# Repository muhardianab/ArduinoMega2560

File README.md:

# ArduinoMega2560
 Making a new Arduino Mega 2560 Board

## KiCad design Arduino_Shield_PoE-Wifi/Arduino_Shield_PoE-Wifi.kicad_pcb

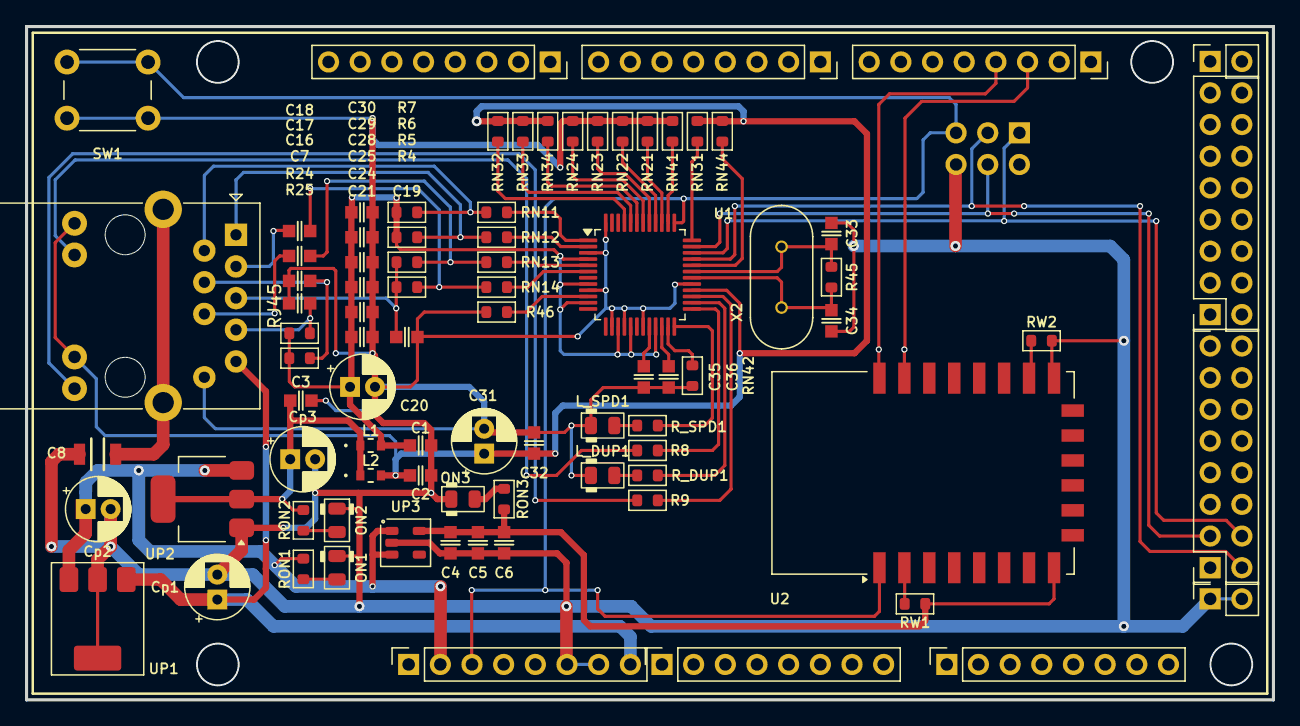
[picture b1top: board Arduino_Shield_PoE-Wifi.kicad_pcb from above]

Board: 2 copper layers, 100.0 x 54.0 mm, 86 parts (1 on the bottom side), 56 nets.

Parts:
ADC1, ADC2: PINHD_1x8_Female; PinSocket_1x08_P2.54mm_Vertical
C1, C2, C3, C4, C5, C6: 100nF_0603_16V; C_0603
C7, C19: 10nF_0603_16V; C_0603
C8: 1nF 2KV 1206; C_1206
C16: 22nF_0603_16V; C_0603
C17, C18: 6.8nF_0603_16V; C_0603
C20, C31: 10uF_25V; CP_Radial_D5.0mm_P2.00mm
C21, C24, C25, C28, C29, C30, C32, C36: 0.1uF_0603_16V; C_0603
C33, C34: 18pF_0603_16V; C_0603
C35: 4.7uF_0603_16V; C_0603
COM1: PINHD_1x8_Female; PinSocket_1x08_P2.54mm_Vertical
Cp1, Cp2, Cp3: 10uF_25V; CP_Radial_D5.0mm_P2.00mm
ICSP1: ICSP_Connector_Female; PinSocket_2x03_P2.54mm_Vertical
J1, J2: Conn_02x08; PinSocket_2x08_P2.54mm_Vertical
J3, J4: PINHD_1x2_Female; PinSocket_1x02_P2.54mm_Vertical
L1, L2: MPZ1608S101ATAH0; IND_1608_TDK
L_DUP1: LED_0805_RED; LED_0805_2012Metric
L_SPD1: LED_0805_RED; LED_0805_2012Metric
ON1, ON2, ON3: LED_0805_Green; LED_0805_2012Metric
PWM1, PWM2: PINHD_1x8_Female; PinSocket_1x08_P2.54mm_Vertical
PWR1: PINHD_1x8_Female; PinSocket_1x08_P2.54mm_Vertical
R4, R5, R6, R7: 49R9_0603; R_0603_1608Metric
R8, R9: 330R_0603; R_0603_1608Metric
R24: 22R_0603; R_0603_1608Metric
R25: 10R_0603; R_0603_1608Metric
R45: 1M_0603; R_0603_1608Metric
R46: 12.4K_0603; R_0603_1608Metric
RJ45: RJ45_Abracon_ARJP11A-MASA-B-A-EMU2; RJ45_Abracon_ARJP11A-MA_Horizontal-edited
RN11, RN12, RN13, RN14: 33R_0603; R_0603_1608Metric
RN21, RN22, RN23, RN24, RN31, RN32, RN33, RN34, RN41, RN42, RN44: 10K_0603; R_0603_1608Metric
RON1, RON2, RON3: 1K_0603; R_0603_1608Metric
RW1, RW2: 10K_0603; R_0603_1608Metric
R_DUP1: 1K_0603; R_0603_1608Metric
R_SPD1: 1K_0603; R_0603_1608Metric
SW1: Push_Button; SW_PUSH_6mm
U1: W5500; LQFP-48_7x7mm_P0.5mm
U2: ESP-12E
UP1: LM7805MP; SOT-223-3_TabPin2
UP2: AMS1117-3.3; SOT-223-3_TabPin2
UP3: AP2112K-3.3TRG1; SOT-23-5
X2: 25MHz 18pF; XTAL_HC49P488W46L1150T500H350

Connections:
+3V3A: C1.1, C20.1, C21.1, C24.1, C25.1, C28.1, C29.1, C30.1, L1.2, R6.2, R7.2, R24.1, R25.1, U1.4 (AVDD), U1.8 (AVDD), U1.11 (AVDD), U1.15 (AVDD), U1.17 (AVDD), U1.21 (AVDD)
+3V3B: C2.1, C31.1, C32.1, L2.2, RJ45.11, RJ45.13, RN31.1, RN32.1, RN33.1, RN34.1, RN44.1, U1.28 (VDD)
+3V3C: C4.1, C5.1, C6.1, RON3.2, RW1.1, U2.8 (VCC), UP3.5 (OUT)
+5V: Cp2.1, ICSP1.2 (VCC), J3.1, J3.2, PWR1.2, PWR1.5, RON1.2, UP1.3 (OUT), UP2.3 (VI), UP3.1 (IN), UP3.3 (EN)
/PB1: ICSP1.3 (SCK), J1.2, U1.33 (SCLK)
/PB2: ICSP1.4 (MOSI), J1.3, U1.35 (MOSI)
/PB3: ICSP1.1 (MISO), J1.4, U1.34 (MISO)
/PowerOverEthernet/ACT_LED: R9.1, U1.27 (ACTLED)
/PowerOverEthernet/DUP_LED: R_DUP1.2, U1.26 (DUPLED)
/PowerOverEthernet/INT: RN31.2, U1.36 (~INT)
/PowerOverEthernet/LINK_LED: R8.1, U1.25 (LINKLED)
/PowerOverEthernet/RCT: C19.2, R4.2, R5.2, RJ45.5 (RCT)
/PowerOverEthernet/RSVD1: RN41.1, U1.38 (RSVD)
/PowerOverEthernet/RSVD2: RN21.1, U1.39 (RSVD)
/PowerOverEthernet/RSVD3: RN22.1, U1.40 (RSVD)
/PowerOverEthernet/RSVD4: RN23.1, U1.41 (RSVD)
/PowerOverEthernet/RSVD5: RN24.1, U1.42 (RSVD)
/PowerOverEthernet/RSVD6: RN42.1, U1.23 (RSVD)
/PowerOverEthernet/RXN1: RN13.1, U1.5 (RXN)
/PowerOverEthernet/RXN2: C17.1, R5.1, RN13.2
/PowerOverEthernet/RXP1: RN14.1, U1.6 (RXP)
/PowerOverEthernet/RXP2: C18.1, R4.1, RN14.2
/PowerOverEthernet/SCS: RN44.2, U1.32 (~SCS)
/PowerOverEthernet/SPD_LED: R_SPD1.2, U1.24 (SPDLED)
/PowerOverEthernet/TCT: C16.2, R25.2, RJ45.4 (TCT)
/PowerOverEthernet/TXN1: RN11.1, U1.1 (TXN)
/PowerOverEthernet/TXN2: R7.1, RJ45.2 (TD-), RN11.2
/PowerOverEthernet/TXP1: RN12.1, U1.2 (TXP)
/PowerOverEthernet/TXP2: R6.1, RJ45.1 (TD+), RN12.2
/RESET1: ICSP1.5 (~{RST), PWR1.3, SW1.1, U1.37 (~RST), U2.1 (~RST)
/RXD1: COM1.3, U2.21 (GPIO3/RXD)
/TXD1: COM1.4, U2.22 (GPIO1/TXD)
Earth: C8.2, RJ45.SH
GND: C1.2, C2.2, C3.2, C4.2, C5.2, C6.2, C7.1, C8.1, C16.1, C19.1, C20.2, C21.2, C24.2, C25.2, C28.2, C29.2, C30.2, C31.2, C32.2, C33.2, C34.2, C35.1, C36.2, Cp1.2, Cp2.2, Cp3.2, ICSP1.6 (GND), J4.1, J4.2, L_DUP1.1 (K), L_SPD1.1 (K), ON1.1 (K), ON2.1 (K), ON3.1 (K), PWR1.6, PWR1.7, R46.2, RJ45.10 (V-), RN21.2, RN22.2, RN23.2, RN24.2, RN41.2, RN42.2, RW2.2, SW1.2, U1.3 (AGND), U1.9 (AGND), U1.14 (AGND), U1.16 (AGND), U1.19 (AGND), U1.29 (GND), U1.48 (AGND), U2.15 (GND), UP1.2, UP2.1 (GND), UP3.2
unnamed: C7.2, R24.2, RJ45.7
unnamed: L_DUP1.2 (A), R_DUP1.1
unnamed: L_SPD1.2 (A), R_SPD1.1
unnamed: ON1.2 (A), RON1.1
unnamed: ON2.2 (A), RON2.1
unnamed: ON3.2 (A), RON3.1
unnamed: R8.2, RJ45.12
unnamed: R9.2, RJ45.14
unnamed: C18.2, RJ45.3 (RD+)
unnamed: C17.2, RJ45.6 (RD-)
unnamed: C36.1, U1.22 (1V2O)
unnamed: R46.1, U1.10 (EXRES1)
unnamed: RN32.2, U1.45 (PMODE0)
unnamed: RN33.2, U1.44 (PMODE1)
unnamed: RN34.2, U1.43 (PMODE2)
unnamed: C35.2, U1.20 (TOCAP)
unnamed: C34.1, R45.2, U1.30 (XI/CLKIN), X2.1
unnamed: C33.1, R45.1, U1.31 (XO), X2.2
unnamed: RW1.2, U2.2 (ADC)
unnamed: RW2.1, U2.16 (GPIO15)
unnamed: C3.1, Cp3.1, L1.1, L2.1, RON2.2, UP2.2 (VO)
VIN: Cp1.1, PWR1.8, RJ45.9 (V+), UP1.1 (IN)

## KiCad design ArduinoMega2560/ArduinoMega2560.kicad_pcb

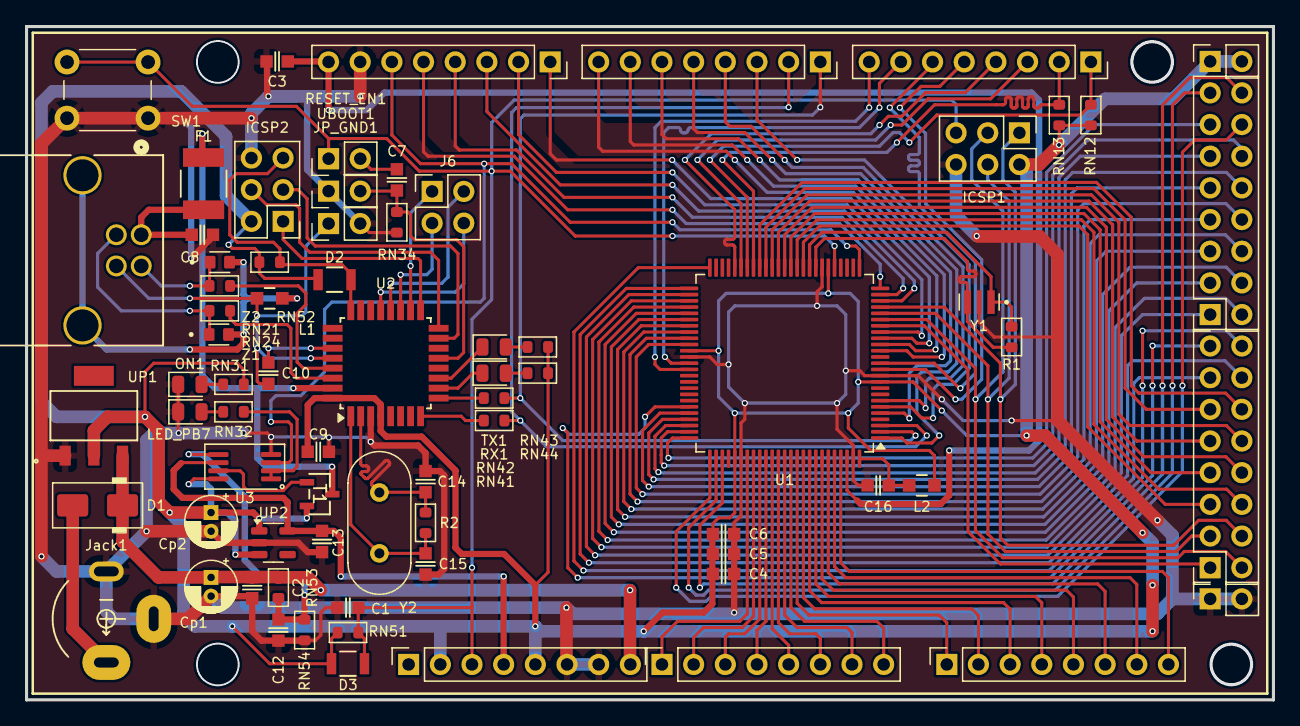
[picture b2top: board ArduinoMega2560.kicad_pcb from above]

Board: 2 copper layers, 100.0 x 54.0 mm, 73 parts (0 on the bottom side), 112 nets.

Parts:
ADC1, ADC2: PINHD_1x8_Female; PinSocket_1x08_P2.54mm_Vertical
C1: 22pF_0603_16V; C_0603
C2, C3, C4, C5, C6, C7, C8, C9, C10, C12, C13, C14, C15, C16: 100nF_0603_16V; C_0603
COM1: PINHD_1x8_Female; PinSocket_1x08_P2.54mm_Vertical
Cp1, Cp2: 47uF_10V; CP_Radial_D4.0mm_P1.50mm
D1: M7; D_SMA
D2, D3: CD1206-S01575; DIODE_CD1206-S01575_BRN
F1: MF-MSMF050-2; FUSE_F050-2
ICSP1, ICSP2: ICSP_Connector; PinHeader_2x03_P2.54mm_Vertical
J1, J2: Conn_02x08; PinSocket_2x08_P2.54mm_Vertical
J3, J4: PINHD_1x2_Female; PinSocket_1x02_P2.54mm_Vertical
J6: PINHD_2x2_Male; PinHeader_2x02_P2.54mm_Vertical
JP_GND1: SolderJumper_2_Open; PinHeader_1x02_P2.54mm_Vertical
Jack1: Barrel_2.0mmPin_PJ064; Barrel_Vert_PJ064_slotted
L1, L2: MH2029-300Y; IND_BOURNS_MH2029
LED_PB7: Yellow 0805; LED_0805_2012Metric
ON1: Green 0805; LED_0805_2012Metric
PWM1, PWM2: PINHD_1x8_Female; PinSocket_1x08_P2.54mm_Vertical
PWR1: PINHD_1x8_Female; PinSocket_1x08_P2.54mm_Vertical
R1, R2: 1M_0603; R_0603_1608Metric
RESET_EN1: SolderJumper_2_Open; PinHeader_1x02_P2.54mm_Vertical
RN12, RN13, RN51, RN52, RN53, RN54: 10K_0603; R_0603_1608Metric
RN21, RN24: 22R_0603; R_0603_1608Metric
RN31, RN32, RN34, RN41, RN42, RN43, RN44: 1K_0603; R_0603_1608Metric
RX1: Yellow 0805; LED_0805_2012Metric
SW1: Push_Button; SW_PUSH_6mm
T1: PMV48XP_215; TO-236_SOT23_NEX
TX1: Green 0805; LED_0805_2012Metric
U1: ATmega2560-16A; TQFP-100_14x14mm_P0.5mm
U2: ATmega8U2-A; TQFP-32_7x7mm_P0.8mm
U3: LMV358IDGK; MSOP-8_3x3mm_P0.65mm
UBOOT1: SolderJumper_2_Open; PinHeader_1x02_P2.54mm_Vertical
UP1: LD1117S50CTR; SOT-223_STM
UP2: LP2985-3.3; SOT-23-5
USB1: UJ2-BH-1-TH; UJ2-BH-1-TH_CUD
Y1: CSTCE16M0V53-R0; OSC_CSTCE16M0V53-R0
Y2: Crystal_16MHz; Crystal_HC49-4H_Vertical
Z1, Z2: CG0603MLC-05E; VARC1608X56N

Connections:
+3V3: C13.1, PWR1.4, U3.6 (-), UP2.5 (VOUT)
+5V: C4.1, C5.1, C6.1, C9.1, Cp2.1, D2.1, D3.1, ICSP1.2 (VCC), ICSP2.2 (VCC), J3.1, J3.2, L2.2, PWR1.2, PWR1.5, RN12.2, RN13.2, RN31.2, RN43.2, RN44.2, RN51.2, RN52.2, T1.2 (S), U1.10 (VCC), U1.31 (VCC), U1.61 (VCC), U1.80 (VCC), U2.4 (VCC), U2.32 (AVCC), U3.8 (V+), UP1.2 (VOUT), UP2.1 (VIN), UP2.3 (ON/~OFF)
/ADC0: ADC2.8, U1.97 (PF0)
/ADC1: ADC2.7, U1.96 (PF1)
/ADC2: ADC2.6, U1.95 (PF2)
/ADC3: ADC2.5, U1.94 (PF3)
/ADC4: ADC2.4, U1.93 (PF4)
/ADC5: ADC2.3, U1.92 (PF5)
/ADC6: ADC2.2, U1.91 (PF6)
/ADC7: ADC2.1, U1.90 (PF7)
/ADC8: ADC1.8, U1.89 (PK0)
/ADC9: ADC1.7, U1.88 (PK1)
/ADC10: ADC1.6, U1.87 (PK2)
/ADC11: ADC1.5, U1.86 (PK3)
/ADC12: ADC1.4, U1.85 (PK4)
/ADC13: ADC1.3, U1.84 (PK5)
/ADC14: ADC1.2, U1.83 (PK6)
/ADC15: ADC1.1, U1.82 (PK7)
/ATmega8U2-MU/MISO2: ICSP2.1 (MISO), U2.17 (PB3)
/ATmega8U2-MU/MOSI2: ICSP2.4 (MOSI), U2.16 (PB2)
/ATmega8U2-MU/SCK2: ICSP2.3 (SCK), U2.15 (PB1)
/ATmega8U2-MU/XT1: C15.2, R2.2, U2.1 (XTAL1), Y2.1
/ATmega8U2-MU/XT2: C14.2, R2.1, U2.2 (PC0/XTAL2), Y2.2
/PA0: J2.16, U1.78 (PA0)
/PA1: J2.15 (-12V), U1.77 (PA1)
/PA2: J2.14 (-12V), U1.76 (PA2)
/PA3: J2.13 (-12), U1.75 (PA3)
/PA4: J2.12 (GND), U1.74 (PA4)
/PA5: J2.11 (GND), U1.73 (PA5)
/PA6: J2.10 (GND), U1.72 (PA6)
/PA7: J2.9 (GND), U1.71 (PA7)
/PB0: J1.1, U1.19 (PB0)
/PB1: ICSP1.3 (SCK), J1.2, U1.20 (PB1)
/PB2: ICSP1.4 (MOSI), J1.3, U1.21 (PB2)
/PB3: ICSP1.1 (MISO), J1.4, U1.22 (PB3)
/PB4: PWM2.3, U1.23 (PB4)
/PB5: PWM2.4, U1.24 (PB5)
/PB6: PWM2.5, U1.25 (PB6)
/PB7: PWM2.6, U1.26 (PB7), U3.3 (+)
/PC0: J2.1, U1.53 (PC0)
/PC1: J2.2, U1.54 (PC1)
/PC2: J2.3, U1.55 (PC2)
/PC3: J2.4, U1.56 (PC3)
/PC4: J2.5 (+12V), U1.57 (PC4)
/PC5: J2.6, U1.58 (PC5)
/PC6: J2.7 (12V), U1.59 (PC6)
/PC7: J2.8 (+12V), U1.60 (PC7)
/PD7: J1.16, U1.50 (PD7)
/PG0: J1.13 (-12), U1.51 (PG0)
/PG1: J1.14 (-12V), U1.52 (PG1)
/PG2: J1.15 (-12V), U1.70 (PG2)
/PG5: PWM1.5, U1.1 (PG5)
/PH3: PWM1.7, U1.15 (PH3)
/PH4: PWM1.8, U1.16 (PH4)
/PH5: PWM2.1, U1.17 (PH5)
/PH6: PWM2.2, U1.18 (PH6)
/PL0: J1.5 (+12V), U1.35 (PL0)
/PL1: J1.6, U1.36 (PL1)
/PL2: J1.7 (12V), U1.37 (PL2)
/PL3: J1.8 (+12V), U1.38 (PL3)
/PL4: J1.9 (GND), U1.39 (PL4)
/PL5: J1.10 (GND), U1.40 (PL5)
/PL6: J1.11 (GND), U1.41 (PL6)
/PL7: J1.12 (GND), U1.42 (PL7)
/Power/CMP: C12.1, RN53.1, RN54.2, U3.5 (+)
/Power/GATE_CMD: T1.1 (G), U3.7
/RXD1: COM1.3, U1.45 (PD2)
/RXD2: COM1.5, U1.12 (PH0)
/RXD3: COM1.7, U1.63 (PJ0)
/SCL: COM1.1, RN12.1, U1.44 (PD1)
/SDA: COM1.2, RN13.1, U1.43 (PD0)
/TXD1: COM1.4, U1.46 (PD3)
/TXD2: COM1.6, U1.13 (PH1)
/TXD3: COM1.8, U1.64 (PJ1)
AREF: C3.1, PWM2.8, U1.98 (AREF)
AVCC: C16.1, L2.1, U1.100 (AVCC)
GND: C1.2, C2.2, C3.2, C4.2, C5.2, C6.2, C8.2, C9.2, C12.2, C13.2, C14.1, C15.1, C16.2, Cp1.2, Cp2.2, ICSP1.6 (GND), ICSP2.6 (GND), J4.1, J4.2, JP_GND1.2 (B), Jack1.2, Jack1.3, LED_PB7.1 (K), ON1.1 (K), PWM2.7, PWR1.6, PWR1.7, RN34.2, RN54.1, SW1.2, U1.11 (GND), U1.32 (GND), U1.62 (GND), U1.81 (GND), U1.99 (GND), U2.3 (GND), U3.4 (V-), UBOOT1.1 (A), UP1.1 (ADJ/GND), UP2.2 (GND), Y1.2
unnamed: C8.1, F1.1, USB1.1
unnamed: D1.2 (A), Jack1.1
unnamed: C10.2, JP_GND1.1 (A), L1.2, U2.28 (UGND), USB1.4
unnamed: L1.1, USB1.5 (SHIELD), USB1.6 (SHIELD), Z1.2, Z2.2
unnamed: LED_PB7.2 (A), RN32.1
unnamed: ON1.2 (A), RN31.1
unnamed: C7.2, RESET_EN1.2 (B)
unnamed: RN21.1, USB1.2, Z1.1
unnamed: RN24.2, USB1.3, Z2.1
unnamed: RN44.1, RX1.2 (A)
unnamed: RX1.1 (K), U2.10 (PD4)
unnamed: RN43.1, TX1.2 (A)
unnamed: TX1.1 (K), U2.11 (PD5)
unnamed: PWM1.6, U1.5 (PE3)
unnamed: PWM1.3, U1.6 (PE4)
unnamed: PWM1.4, U1.7 (PE5)
unnamed: R1.2, U1.34 (XTAL1), Y1.1
unnamed: R1.1, U1.33 (XTAL2), Y1.3
unnamed: RN24.1, U2.29 (D+)
unnamed: RN21.2, U2.30 (D-)
unnamed: RN41.1, U2.8 (PD2)
unnamed: RN42.1, U2.9 (PD3)
unnamed: C10.1, U2.27 (UCAP)
unnamed: C7.1, RN34.1, U2.13 (~HWB/PD7), UBOOT1.2 (B)
unnamed: RN32.2, U3.1, U3.2 (-)
PB4: J6.1, U2.18 (PB4)
PB5: J6.3, U2.19 (PB5)
PB6: J6.2, U2.20 (PB6)
PB7: J6.4, U2.21 (PB7)
RESET1: C1.1, D3.2, ICSP1.5 (~{RST), PWR1.3, RESET_EN1.1 (A), RN51.1, SW1.1, U1.30 (~RESET)
RESET2: D2.2, ICSP2.5 (~{RST), RN52.1, U2.24 (PC1/~RESET)
RXD0: PWM1.1, RN42.2, U1.2 (PE0)
TXD0: PWM1.2, RN41.2, U1.3 (PE1)
USBVCC: F1.2, T1.3 (D), U2.31 (UVCC)
VIN: C2.1, Cp1.1, D1.1 (K), PWR1.8, RN53.2, UP1.3 (VIN)

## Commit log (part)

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2024-06-09 First upload
2025-03-16 Rearrange files and folders
2025-03-16 Annotation problem
2025-03-16 Daily update
2025-03-19 Update label
2025-03-19 Update label and check dimension size
2025-03-20 Confirming the dimension
2025-03-20 Tracing
2025-03-20 Update Trace
2025-03-21 Update tracing
2025-03-27 Update daily
2025-03-29 1st update
2025-04-21 Update
    Using Rev3
2025-05-02 Last trace update
2025-05-06 Update footprint and silkscree
    next, fixing the trace on the pinheader
2025-05-07 Final
2025-05-08 Checking Eth PoE
2025-05-18 Tuning serial and crystal tracks
2025-05-18 Update Eth
2025-06-12 Update shield
2025-06-21 Change the wifi module
    Replace ATWINC with ESP8266
2025-07-10 fixing schematics
    Fix using ESP8266 12-E
2025-07-26 Update fix schematics
2026-02-05 Update Done Shield PoE
